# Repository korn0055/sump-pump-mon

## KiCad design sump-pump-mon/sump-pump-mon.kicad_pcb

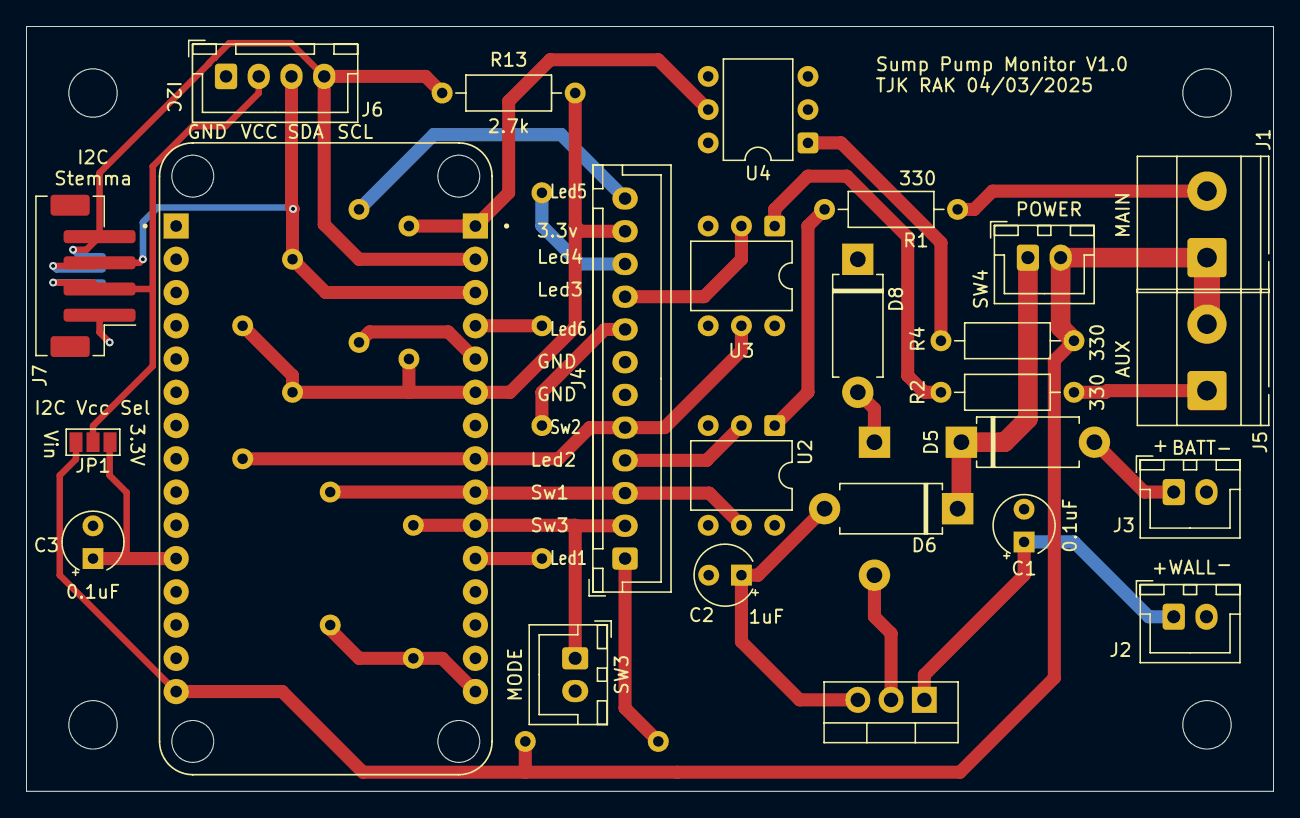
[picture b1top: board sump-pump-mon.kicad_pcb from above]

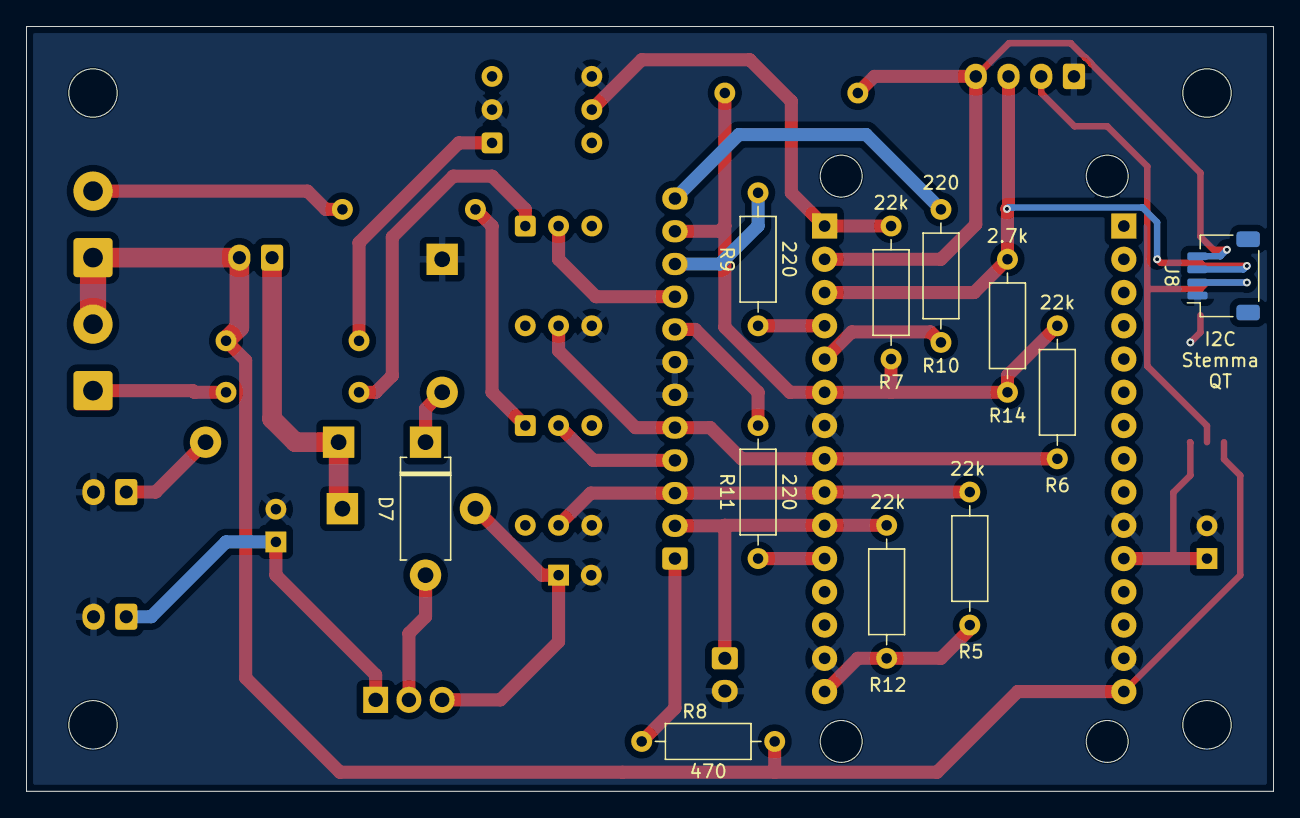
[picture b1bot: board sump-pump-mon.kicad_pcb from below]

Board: 2 copper layers, 95.3 x 58.4 mm, 40 parts (11 on the bottom side), 30 nets.

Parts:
A1: 113990105; SEEED_113990105
C1, C3: 0.1uF; CP_Radial_Tantal_D4.5mm_P2.50mm
C2: 1uF; CP_Radial_Tantal_D4.5mm_P2.50mm
D5, D6: D_Schottky; D_DO-15_P10.16mm_Horizontal
D7, D8: D; D_DO-15_P10.16mm_Horizontal
H1, H2, H3, H4: MountingHole; MountingHole_3.7mm
J1: Main Input; TerminalBlock_Phoenix_MKDS-1,5-2-5.08_1x02_P5.08mm_Horizont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
J2: Wall Power; JST_XH_B2B-XH-A_1x02_P2.50mm_Vertical
J3: Battery; JST_XH_B2B-XH-A_1x02_P2.50mm_Vertical
J4: Display_Conn; JST_XH_B12B-XH-A_1x12_P2.50mm_Vertical
J5: Aux Input; TerminalBlock_Phoenix_MKDS-1,5-2-5.08_1x02_P5.08mm_Horizont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
J6: I2C; JST_XH_B4B-XH-A_1x04_P2.50mm_Vertical
J7: I2C Stemma; JST_PH_B4B-PH-SM4-TB_1x04-1MP_P2.00mm_Vertical
J8: I2C Stemma QT; JST_SH_SM04B-SRSS-TB_1x04-1MP_P1.00mm_Horizontal
JP1: SolderJumper_3_Open; SolderJumper-3_P1.3mm_Open_Pad1.0x1.5mm_NumberLabels
R1, R2, R4: 330; R_Axial_DIN0207_L6.3mm_D2.5mm_P10.16mm_Horizontal
R5, R6, R7, R12: 22k; R_Axial_DIN0207_L6.3mm_D2.5mm_P10.16mm_Horizontal
R8: 470; R_Axial_DIN0207_L6.3mm_D2.5mm_P10.16mm_Horizontal
R9, R10, R11: 220; R_Axial_DIN0207_L6.3mm_D2.5mm_P10.16mm_Horizontal
R13, R14: 2.7k; R_Axial_DIN0207_L6.3mm_D2.5mm_P10.16mm_Horizontal
SW3: MODE; JST_XH_B2B-XH-A_1x02_P2.50mm_Vertical
SW4: POWER; JST_XH_B2B-XH-A_1x02_P2.50mm_Vertical
U1: L7805; TO-220-3_Vertical
U2, U3, U4: 4N25; DIP-6_W7.62mm

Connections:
+3.3V: A1.J1_11 (3V3), A1.J2_6 (3V3), A1.J2_15 (3V3), C3.1, J4.11, JP1.1 (A), R5.1, R6.1, R7.1, R12.1, R13.1, R14.1
GND: A1.J1_10 (GND), A1.J1_14 (GND), A1.J2_7 (GND), A1.J2_14 (GND), C1.2, C2.2, C3.2, D8.1 (K), J2.2, J3.2, J4.6, J4.7, J6.1, J7.1, J8.1, SW3.2 (B), U2.4, U3.4, U4.2, U4.4
Green_Button: A1.J2_9 (D6), J4.3, R5.2, U2.5
LED_6V: J4.1, R8.2
LED_AUX: J4.9, U3.2
LED_BLUE: J4.8, R11.2
LED_GREEN: J4.10, R9.2
LED_MAIN: J4.4, U2.2
LED_YELLOW: J4.12, R10.2
Mode: A1.J2_10 (D7), J4.2, R12.2, SW3.1 (A)
unnamed: A1.J2_2 (D1), J6.4, J7.4, J8.4, R13.2
unnamed: A1.J2_3 (D2), J6.3, J7.3, J8.3, R14.2
unnamed: A1.J2_4 (D3), R9.1
unnamed: A1.J2_5 (D4), R10.1
unnamed: A1.J2_11 (D8), R11.1
unnamed: D5.2 (A), J3.1
unnamed: D5.1 (K), D6.1 (K), SW4.1 (A)
unnamed: C2.1, D6.2 (A), U1.3 (OUT)
unnamed: D7.2 (A), U1.2 (GND)
unnamed: D7.1 (K), D8.2 (A)
unnamed: J1.2, R1.1
unnamed: C1.1, J2.1, U1.1 (IN)
unnamed: J5.1, R2.1
unnamed: J6.2, J7.2, J8.2, JP1.2 (C)
unnamed: R1.2, U2.1
unnamed: R2.2, U3.1
unnamed: R4.2, U4.1
Power_Failure: A1.J2_1 (D0), R7.2, U4.5
Vin: A1.J1_15 (VIN), J1.1, J5.2, JP1.3 (B), R4.1, R8.1, SW4.2 (B)
Yellow_Button: A1.J2_8 (D5), J4.5, R6.2, U3.5

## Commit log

2025-04-03 Initial commit - before removing LEDs
2025-04-03 Rough parts placement and partial routing
2025-04-04 Routing complete
2025-04-04 add gerbers
2025-04-04 add values to silkscreen
2025-04-04 Change R14 value to silk layer
2025-04-08 Redid layout to shrink size and add ground plane
2025-04-08 Shrink layout a bit more
2025-04-08 Layout polishing
2025-04-08 Update gerbers
2025-04-08 Fix missing connection, move C1 to top, shift J2 down
2025-04-08 Add GND to I2C connector
2025-04-09 Add Stemma connectors; Add 3d models; Cleanup silk
2025-04-09 Enter OSHPark design rules; thicken silk to meet requirement
2025-04-09 Export step and gerbers
2025-04-10 Move drill origin; export step with silk and center origin
2025-04-10 Add note about mode switch
2025-04-17 updated silkscreen & renamed nets
